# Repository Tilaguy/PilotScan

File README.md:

## PILOT SCAN
---
### 1. Descripción

En este repositorio se encuentran alojados los algoritmos necesarios para elaborar una interfaz de comunicación codificada con capacidad de detección de errores, durante el proceso de envío. Esta interfaz hace parte del sistema titulado **PilotScan\***, el cual consta de un sistema central de procesamiento y un sistema de respaldo que monitora de forma continua, el estado del sistema tanto a nivel hardware como software, además tiene la capacidad de realizar acciones indicadas por sistema central, sobre los diferentes módulos que conforman el sistema.

Para el sistema central de procesamiento, se usa una **Intel®️ NUC Board** con Linux 16.04 server. Para el sistema de respaldo se emplea un **dsPIC 30F4011**, el cual conecta diferentes sensores analógicos y digitales, tiene la capacidad de habilitar y deshabilitar fuentes reguladas de *12 V* y *24 V*, además de emitir mensajes al usuario a través de una bocina y leds RGB programables.

**\*** La información detallada del sistema se encuentra alojada en el repositorio: \ link \

---
## 2. Repository organization
Este repositorio se encuentra organizado de la siguiente forma:

### 2.1. PIC
* *Timer.c*:  Este archivo genera un reloj a frecuencia constante en un microcontrolador **PIC 16f506**, el cual sirve como base de tiempo para garantizar que el sistema de firmware está en funcionamiento.
### 2.2. Python
Estos archivos son nodos para ROS, los cuales interactúan entre sí por medio de tópicos para el monitoreo, procesamiento y acción sobre los diferentes módulos que conforman el sistema **PilotScan**.

* *Firmware.py*:  Nodo encargado de la recepción y transmisión serial con el sistema de respaldo.

* *Monitoring.py*:  Nodo encargado del procesamiento, codificación y decodificación de la información mediante protocolos diseñados para cada caso específico.

* *Resources.py*:  Nodo que lee la información del estado del sistema y la publica por medio de tópicos separados como el estado de memoria, la temperatura de los núcleos y entre otros.

### 2.3. dsPIC
#### 2.3.1. Include

* *ports.h*:  Librería para hacer asignaciones de pines según su uso y declaración de variables globales.

* *NOTAS.C*:  Librería para definir el tiempo de una nota usada por el Buzzer en el sistema.

* *TONOS.C*:  Librería donde se definen las notas musicales separado por octavas en 4 grupos de frecuencias diferentes.

* *SerialProtocol.h*:  Librería encargada de la codificación y decodificación de la información mediante protocolos diseñados para cada caso específico.

* *Hadware_actions.h*:  Librería usada para generar acciones o notificaciones del estado del sistema mediante el buzzer o los LEDs RGB.

* *Nuc_interface.h*:  Librería usada para encender y apagar el sistema de cómputo central.

* *I2C_DIR*:  Libreria que contiene las definiciones de direcciones I2C para la comunicación con algunos sensores, las funciones correspondientes para establecer dicha comunicación.

#### 2.3.2. Main
En el archivo main.c se hace uso de las librerías mencionadas anteriormente, se realiza la configuración de los diferentes periféricos de microcontrolador como modulo ADC, I2C, RS232, entre otros. Adicionalmente, se realiza la configuración y activación de interrupciones.

---

## 3. Protocolo de comunicación serial **computador-dsPIC**
El protocolo que se usa para la comunicación entre el microcontrolador y el computador genera un número que codifica la información en hexadecimal, esta codificación depende de quién es emisor del mensaje, esta codificación se explica más detalladamente a continuación. Además, el protocolo cuenta con un Byte de inicio (*'$'*) que indica el comienzo del mensaje y un salto de línea (*'\n'*) que informa el final. En cualquier caso, si los Bytes de información toman los valores de 0, significa un error en la codificación.

### 3.1. Protocolo de envió desde la Intel® NUC Board
Este protocolo se construye a partir de una tabla de valores constantes, los cuales indican el estado del sistema en diferentes ámbitos tales como: monitoreo y control de las fuentes, la comunicación de problemas de ejecución y otros requerimientos necesarios para el correcto funcionamiento del sistema. Dicho protocolo consta de dos Byte, los cuales codifican la información.

El primer Byte (**data1**) indica el origen de la información (VN-300, LiDAR, estado del sistema, etc.) de la cual se está dando a conocer su estado. El segundo Byte (**data2**) informa el estado y da idea de cómo debe proceder el microcontrolador. Los dos Bytes restantes corresponden al checksum, quien funciona como sistema de detección de errores en el proceso de comunicación, pues dichos Bytes deben corresponden a la suma de los dos primeros (**dato1+dato2**).

Cada mensaje es interpretado por el microcontrolador quien efectúa algún tipo de acción, ya sea realizando un encendido o apagado de algún elemento, activando alertas auditivas o alertas visuales a través de leds RGB.

* **P. ej.** Si la *temperatura media de los núcleos del sistema de cómputo* esta entre 35 °C y 40 °C, en microcontrolador debe *encender los ventiladores* en cierta forma particular.
  * Mensaje enviado:
  ~~~
  data1 =      0x4
  data2 =      0xE
  checksum =   0x12
  mensaje =    '$19986\n'
  ~~~
  * Acción tomada por el microcontrolador:
  ~~~
  - Encendido de ventilador ( PWM ~ 60% )
  - LED RGB 4 ([R,G,B] = [25,128,0])
  ~~~
#### Tabla 3.1.1. Mensajes del sistema.

data 1 | data 2 | message | meaning
-- | -- | -- | -- 
0 | 0 |         |Reserve
0 | 1 | sys-on_24 |	Turn-on source 24V
0 | 2 | sys-off_12 |Turn-off source 12V
0 | 3 | sys-off_24 |Turn-off source 24V
0 | 4 | sys-mem_E |	Memory problem
0 | 5 | sys-on_m8 |	Turn LiDAR on
0 | 6 | sys-on_tty |Turn all tty ports on
0 | 7 |
0 | 8 |
0 | 9 |
0 | A |
0 | B |
0 | C |
0 | D |
0 | E |
0 | F |

#### Tabla 3.1.2. Mensajes del estado del VN300.
data 1 | data 2 | message | meaning | R | G | B |LED
-- | -- | -- | -- | -- | -- | -- |--
1 | 0 |         |Reserve|0|0|0|L1
1 | 1 | VN300-NC |	VN300 No Connected|240|0|0|L1
1 | 2 | VN300-Start |VN 300 Starting|240|128|0|L1
1 | 3 | VN300-<25 | VN300 <25%|50|0|240|L1
1 | 4 | VN300-<50 |25% < VN300 <50%|50|80|160|L1
1 | 5 | VN300-<75 |	50% < VN300 <75|50|160|80|L1
1 | 6 | VN300->75 |VN300 >75%|50|240|0|L1
1 | 7 |VN300-Work | VN300 Working|0|240|0|L1
1 | 8 |
1 | 9 |
1 | A |
1 | B |
1 | C |
1 | D |
1 | E |
1 | F |

#### Tabla 3.1.3. Mensajes del estado del LiDAR M8.
data 1 | data 2 | message | meaning | R | G | B |LED
-- | -- | -- | -- | -- | -- | -- | --
2 | 0 |         |Reserve|0|0|0|L2
2 | 1 | M8-NC |	M8 No Ping|240	|0|0|L2
2 | 2 | M8-Start |M8 Starting|240|128|0|L2
2 | 3 |
2 | 4 |
2 | 5 |
2 | 6 |
2 | 7 |M8-Work | M8 Working|0|240|0 |L2
2 | 8 |
2 | 9 |
2 | A |
2 | B |
2 | C |
2 | D |
2 | E |
2 | F |
#### Tabla 3.1.4. Mensajes del estado de la cámara.
data 1 | data 2 | message | meaning
-- | -- | -- | --
3 | 0 |         |Reserve
3 | 1 | CAM-NC | CAM No Connected
3 | 2 | CAM-Start |CAM Starting
3 | 3 |  |
3 | 4 |  |
3 | 5 |  |
3 | 6 |  |
3 | 7 |CAM-Work | CAM Working
3 | 8 |
3 | 9 |
3 | A |
3 | B |
3 | C |
3 | D |
3 | E |
3 | F |
#### Tabla 3.1.5. Mensajes del control Fuzzy para temperatura.
data 1 | data 2 | message | meaning | R | G | B|LED
-- | -- | -- | -- | -- | -- | -- |--
3 | 0 |  |Reserve|0|0|0|L4
3 | 1 |   
3 | 2 |  
3 | 3 |  
3 | 4 |  
3 | 5 |  
3 | 6 |  
3 | 7 |   
3 | 8 |
3 | 9 |
3 | A |
3 | B |
3 | C |FUZZ-T1|>25°|13	|0|	125|L4
3 | D |FUZZ-T2|>30°|113|	0|	125|L4
3 | E |FUZZ-T3|>35°|255|	128|	0|L4
3 | F |FUZZ-T4|>40°|250|0|	0|L4
#### Tabla 3.1.6. Mensajes de error de memoria.
data 1 | data 2 | message | meaning | R | G | B |LED
-- | -- | -- | -- | -- | -- | -- | --
A | 0 |  |Reserve|0|0|0|L3
A | 1 | memo-RAM_E1 |RAM alert1|255|64|64|L3
A | 2 | memo-RAM_E2 |RAM alert2|255|0|0|L3
A | 3 |
A | 4 |
A | 5 |
A | 6 | memo-ROM_E1 |ROM alert1|64|133|255 |L3
A | 7 | memo-ROM_E2 |ROM alert2|64|64|255|L3
A | 8 | memo-ROM_E3 |ROM alert3|0|0|255|L3
A | 9 |
A | A |
A | B |
A | C |
A | D |
A | E |
A | F |
### 3.2. Protocolo de envío desde el dsPIC
Este protocolo se construye a partir de una tabla de valores constantes y los datos numéricos codificados en hexadecimal, que informan al computador sobre las variables medidas por el microcontrolador. Dicho protocolo consta de tres Bytes que codifican la información, los cuales son enviados al computador para ponerlo en conocimiento de los valores numéricos de las variables fundamentales para el funcionamiento de las tarjetas.

El primer Byte corresponde al tipo de información (**command**) como corrientes, voltajes, etc., y su origen. Los siguientes dos Bytes son la información numérica codificada (**data1**, **data2**), la cual puede ser entera o flotante. Adicionalmente, existen dos Bytes corresponden al checksum, el cual permite verificar la información transmitida como protocolo de detección de errores y además permite conocer si el dato numérico enviado es un entero con rango [0, 255] (**command+data1+data2+0x05**), o un flotante con una cifra decimal de precisión (**command+data1+data2**).

* **P. ej.** La *corriente proveniente de la fuente de 5 V* medida por el sensor es de *0.45 A*, a su vez *el altímetro* detecta una altura de *64 m*.
  * Mensaje 1 enviado:
  ~~~
  Command =    0x1
  data1 =      0x0
  data2 =      0x4
  checksum =   0x05
  mensaje =    '$66565\n'
  ~~~
  * Mensaje 2 enviado:
  ~~~
  Command =    0xD
  data1 =      0x4
  data2 =      0x0
  checksum =   0x16
  mensaje =    '$868374\n'
  ~~~
#### Tabla 3.2.1. Variables medidas codificadas.
   
Command|	data1|	data2|	meaning|
|--|--|--|--|
0|	|	|	Reserved|
1|	x|	y|	current source 5 "x.y"|
2|	x|	y|	current source 12 "x.y"|
3|	x|	y|	current source 24 "x.y"|
4|	x|	y|	current source battery "x.y"|
5|	x|	y|	Voltage source 5 "x.y"|
6|	x|	y|	Voltage source 12 "x.y"|
7|	x|	y|	Voltage source 24 "x.y"|
8|	x|	y|	Voltage source Battery "x.y"|
9|	x|	y|	Temperature LiDAR|
A|	x|	y|	Temperature dsPIC|
B|	x|	y|	Temperature DC|
C|	x|	y|	Temperature xx|
D|	x|	y|	Hight|

#### Tabla 3.2.2. Estado de los módulos del sistema.
|Command|	data1|	data2|	meaning|
|--|--|--|--|
|F	|0	|0	|Reserved|
|F	|0	|1	|12 V is on|
|F	|1	|0	|24 V is on|
|F	|1	|1	|All sources are on|
|F	|0	|2	|12 V is going to shut it down in 1 m|
|F	|2	|0	|24 V is going to shut it down in 1 m|
|F	|2	|2	|All sources are going to shut it down in 1 m|
|F	|0	|3	|shut LiDAR down |
|F	|3	|0	|close all tty ports|
|F	|3	|3	|shut ROS down |
|F	|0	|4	|turn LiDAR on|
|F	|4	|0	|turn all tty ports on|
|F	|4	|4	|turn ROS on|

---

### 4. Software requirements for computer

#### 4.1. ROS Kinetic instaliation

To install robot operating system (ROS) in the kinetic version for ubuntu 16.04, you should follow the steeps descrived in http://wiki.ros.org/kinetic/Installation/Ubuntu.

#### 4.2. VN300 ROS node

The installing of VN-300 node for ROS, it begins with downloading the repository in *workspace/src* directory.
~~~
$ git clone https://github.com/HaroldMurcia/vectornav.git
~~~
Afeter that, you have to compilate the *workspace* directory.
~~~
$ catkin_make
$ source devel/setup.bash
~~~
Finaly, The node could be launched with ROS instrction:
~~~
$ roslaunch vectornav vectornav.launch
~~~
#### 4.3. Quanergy M8 liDAR

To be able to launch the ROS node of Quanergy M8 LiDAR, you have to follow the steeps of the next repository.
https://github.com/mfassler/python3-quanergyM8

#### 4.1. System_monitor Installation
La instalación del System_monitor node para ROS: (https://github.com/RobotnikAutomation/system_monitor)

Dentro de la carpeta *src* del *workspace*, se debe descargar el *system_monitor* usando la siguiente instrucción:
~~~
$ git clone https://github.com/RobotnikAutomation/system_monitor
~~~
Es necesario instalar algunas dependencias adicionales para su ejecución,
~~~
$ sudo apt-get install sysstat ifstat ntpdate
~~~
Luego, se compila en el *workspace* y se asigna el directorio *devel*,
~~~
$ catkin_make
$ source devel/setup.bash
~~~
Por último, para lanzar el nodo se usa la instrucción:
~~~
$ roslaunch system_monitor system_monitor.launch
~~~

---
### 5. Authors.

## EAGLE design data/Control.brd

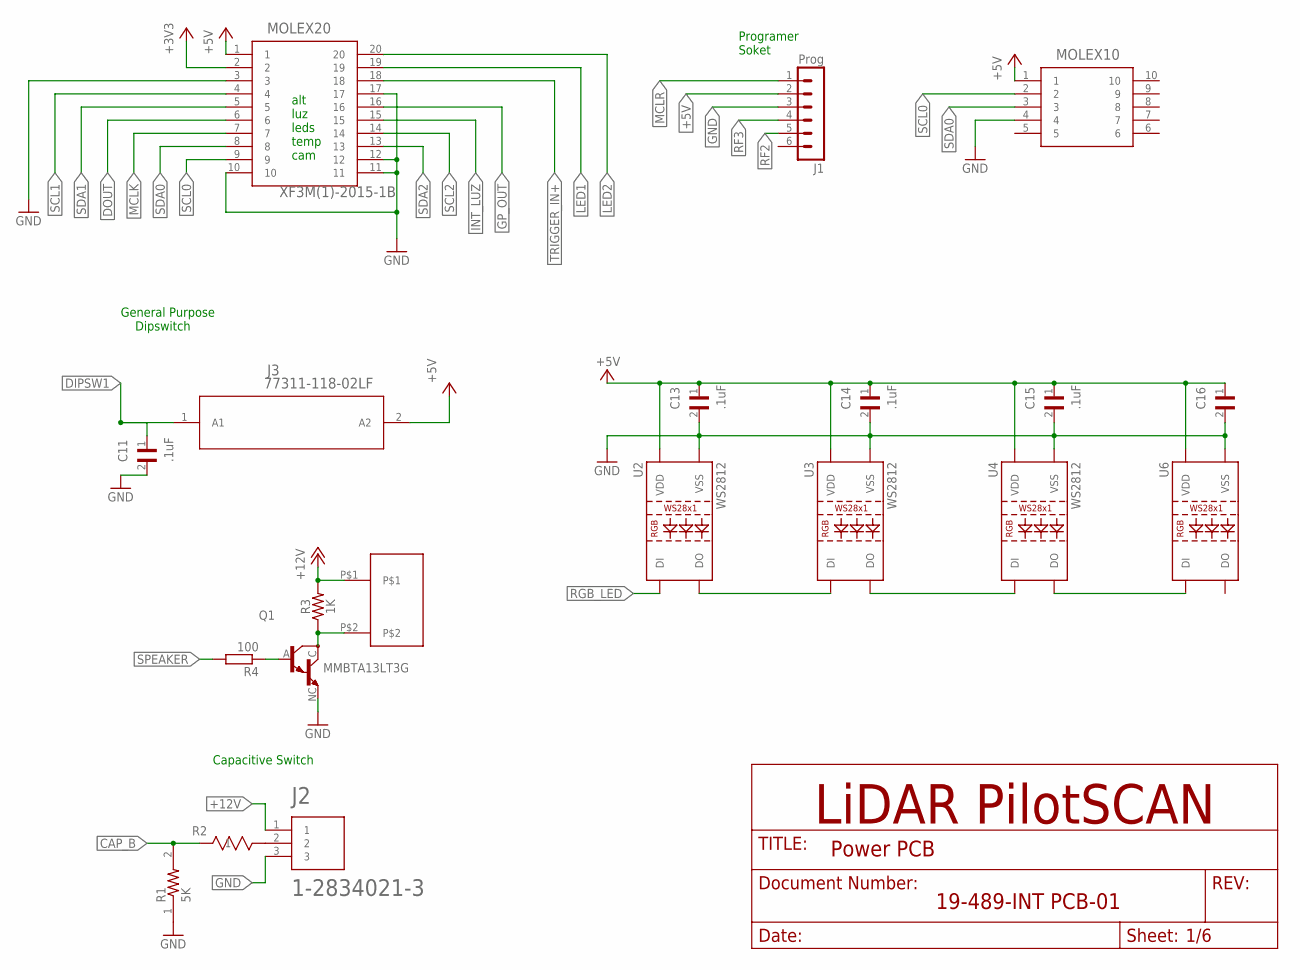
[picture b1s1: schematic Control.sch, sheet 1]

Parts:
BUZZ1: PS1240P02BT
C11, C13, C14, C15, C16: .1uF; CAPC2012X140N
J1: Prog; MA06-1
J2: 1-2834021-3; CONN_1-2834021-3
J3: 77311-118-02LF
MOLEX10: 522071060
MOLEX20: XF3M(1)-2015-1B
Q1: MMBTA13LT3G
R1: 5K; RESC2012X60
R2: 6K8; RES_RC0201_P6XP3
R3: 1K; AXIAL-0.3
R4: 100; RMCF0805JT270R
U2, U3, U4, U6: WS2812; LED-TRICOLOR-5050-IC

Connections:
+3V3: MOLEX20.2; also elsewhere on the board
+5V: C13.1, C14.1, C15.1, C16.1, J1.2, J3.2 (A2), MOLEX10.1, MOLEX20.1, U2.3 (VDD), U2.5 (VDD), U3.3 (VDD), U3.5 (VDD), U4.3 (VDD), U4.5 (VDD), U6.3 (VDD), U6.5 (VDD); also elsewhere on the board
+12V: BUZZ1.P$1, J2.1, R3.P$2 (2); also elsewhere on the board
CAP_B: R1.2, R2.1; also elsewhere on the board
DIPSW1: C11.1, J3.1 (A1); also elsewhere on the board
DOUT: MOLEX20.6; also elsewhere on the board
GND: C11.2, C13.2, C14.2, C15.2, C16.2, J1.3, J2.3, MOLEX10.4, MOLEX20.3, MOLEX20.10, MOLEX20.11, MOLEX20.12, MOLEX20.17, Q1.NC (E), R1.1, U2.6 (VSS), U3.6 (VSS), U4.6 (VSS), U6.6 (VSS); also elsewhere on the board
GP_OUT: MOLEX20.16; also elsewhere on the board
INT_LUZ: MOLEX20.15; also elsewhere on the board
LED1: MOLEX20.19; also elsewhere on the board
LED2: MOLEX20.20; also elsewhere on the board
MCLK: MOLEX20.7; also elsewhere on the board
MCLR: J1.1; also elsewhere on the board
unnamed: Q1.A (B), R4.1
unnamed: BUZZ1.P$2, Q1.C, R3.P$1 (1)
unnamed: J2.2, R2.2
unnamed: U2.1 (DO), U3.2 (DI)
unnamed: U3.1 (DO), U4.2 (DI)
unnamed: U4.1 (DO), U6.2 (DI)
RF2: J1.5; also elsewhere on the board
RF3: J1.4; also elsewhere on the board
RGB_LED: U2.2 (DI); also elsewhere on the board
SCL0: MOLEX10.2, MOLEX20.9; also elsewhere on the board
SCL1: MOLEX20.4; also elsewhere on the board
SCL2: MOLEX20.14; also elsewhere on the board
SDA0: MOLEX10.3, MOLEX20.8; also elsewhere on the board
SDA1: MOLEX20.5; also elsewhere on the board
SDA2: MOLEX20.13; also elsewhere on the board
SPEAKER: R4.2; also elsewhere on the board
TRIGGER_IN+: MOLEX20.18; also elsewhere on the board

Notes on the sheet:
Programer Soket
General Purpose Dipswitch
Capacitive Switch
alt luz leds temp cam

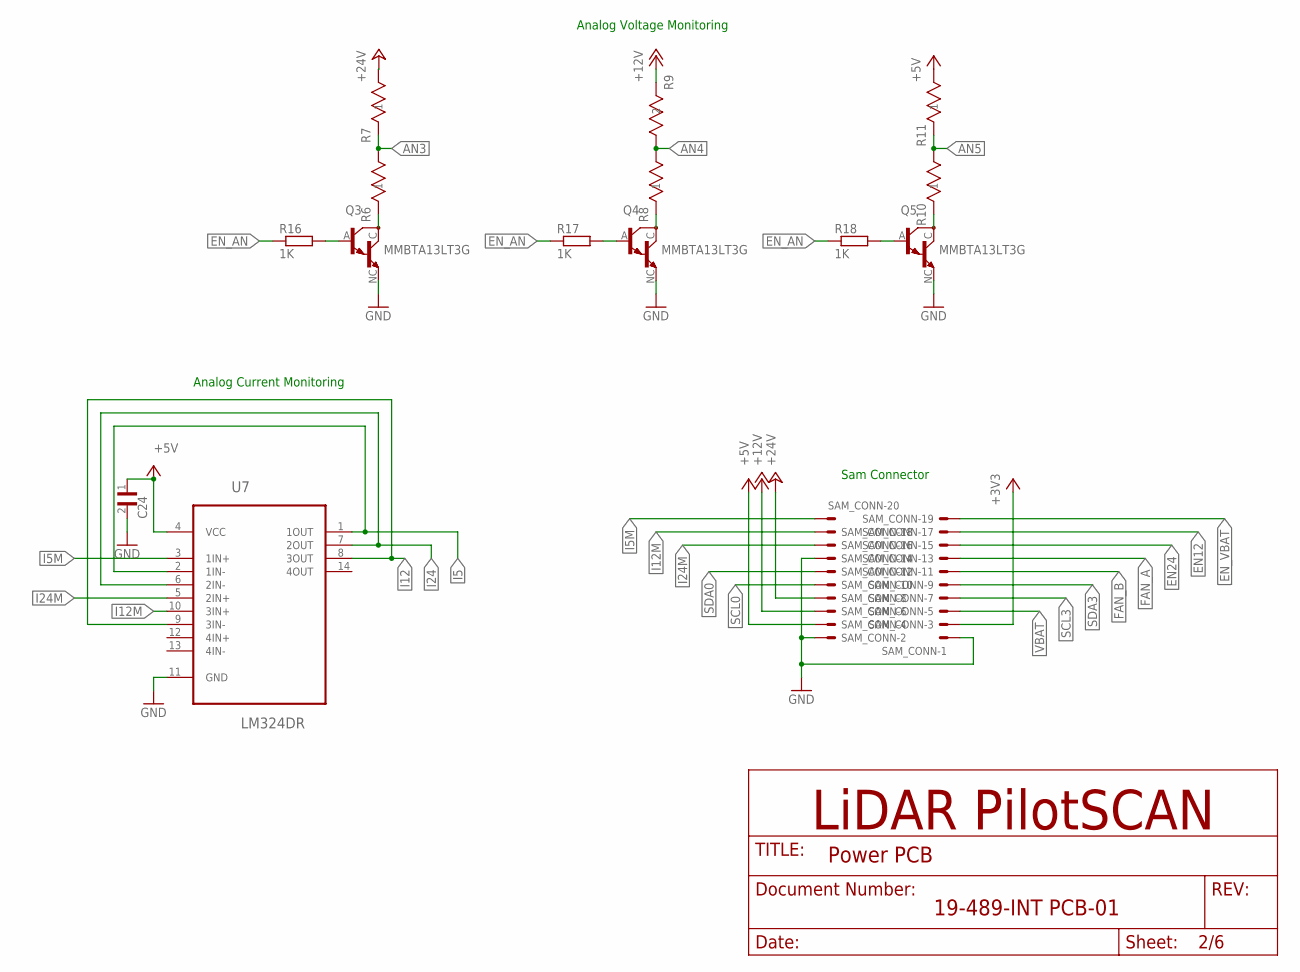
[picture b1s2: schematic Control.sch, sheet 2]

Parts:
C24: 08056C104JAZ2A; CAPC2012X140N
Q3, Q4, Q5: MMBTA13LT3G
R6, R8, R10: 1K8; RES_RC0201_P6XP3
R7: 18K; RES_RC0201_P6XP3
R9: 8K2; RES0805_CRG_TYCO-L
R11: 1K5; YAG_R0201
R16, R17, R18: 1K; RMCF0805FT1K00
SAM_CONN: IPT1-110-01-L-D
U7: LM324DR; SOIC127P600X175-14N

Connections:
+3V3: SAM_CONN.P$3; also elsewhere on the board
+5V: C24.1, R11.2, SAM_CONN.P$4, U7.4 (VCC); also elsewhere on the board
+12V: R9.2, SAM_CONN.P$6; also elsewhere on the board
+24V: R7.2, SAM_CONN.P$8
AN3: R6.2, R7.1; also elsewhere on the board
AN4: R8.2, R9.1; also elsewhere on the board
AN5: R10.2, R11.1; also elsewhere on the board
EN12: SAM_CONN.P$17; also elsewhere on the board
EN_AN: R16.1, R17.1, R18.1; also elsewhere on the board
EN_VBAT: SAM_CONN.P$19; also elsewhere on the board
ESRDTFYGHUJI: Q4.C, R8.1
FAN_A: SAM_CONN.P$13; also elsewhere on the board
FAN_B: SAM_CONN.P$11; also elsewhere on the board
GND: C24.2, Q3.NC (E), Q4.NC (E), Q5.NC (E), SAM_CONN.P$1, SAM_CONN.P$2, SAM_CONN.P$14, U7.11 (GND); also elsewhere on the board
I5: U7.1 (1OUT), U7.2 (1IN-); also elsewhere on the board
I5M: SAM_CONN.P$20, U7.3 (1IN+)
I12: U7.8 (3OUT), U7.9 (3IN-); also elsewhere on the board
I12M: SAM_CONN.P$18, U7.10 (3IN+)
I24: U7.6 (2IN-), U7.7 (2OUT); also elsewhere on the board
I24M: SAM_CONN.P$16, U7.5 (2IN+)
unnamed: Q3.A (B), R16.2
unnamed: Q3.C, R6.1
unnamed: Q4.A (B), R17.2
unnamed: Q5.C, R10.1
unnamed: Q5.A (B), R18.2
SCL0: SAM_CONN.P$10; also elsewhere on the board
SCL3: SAM_CONN.P$7; also elsewhere on the board
SDA0: SAM_CONN.P$12; also elsewhere on the board
SDA3: SAM_CONN.P$9; also elsewhere on the board
VBAT: SAM_CONN.P$5; also elsewhere on the board

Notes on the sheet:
Analog Voltage Monitoring
Analog Current Monitoring
Sam Connector

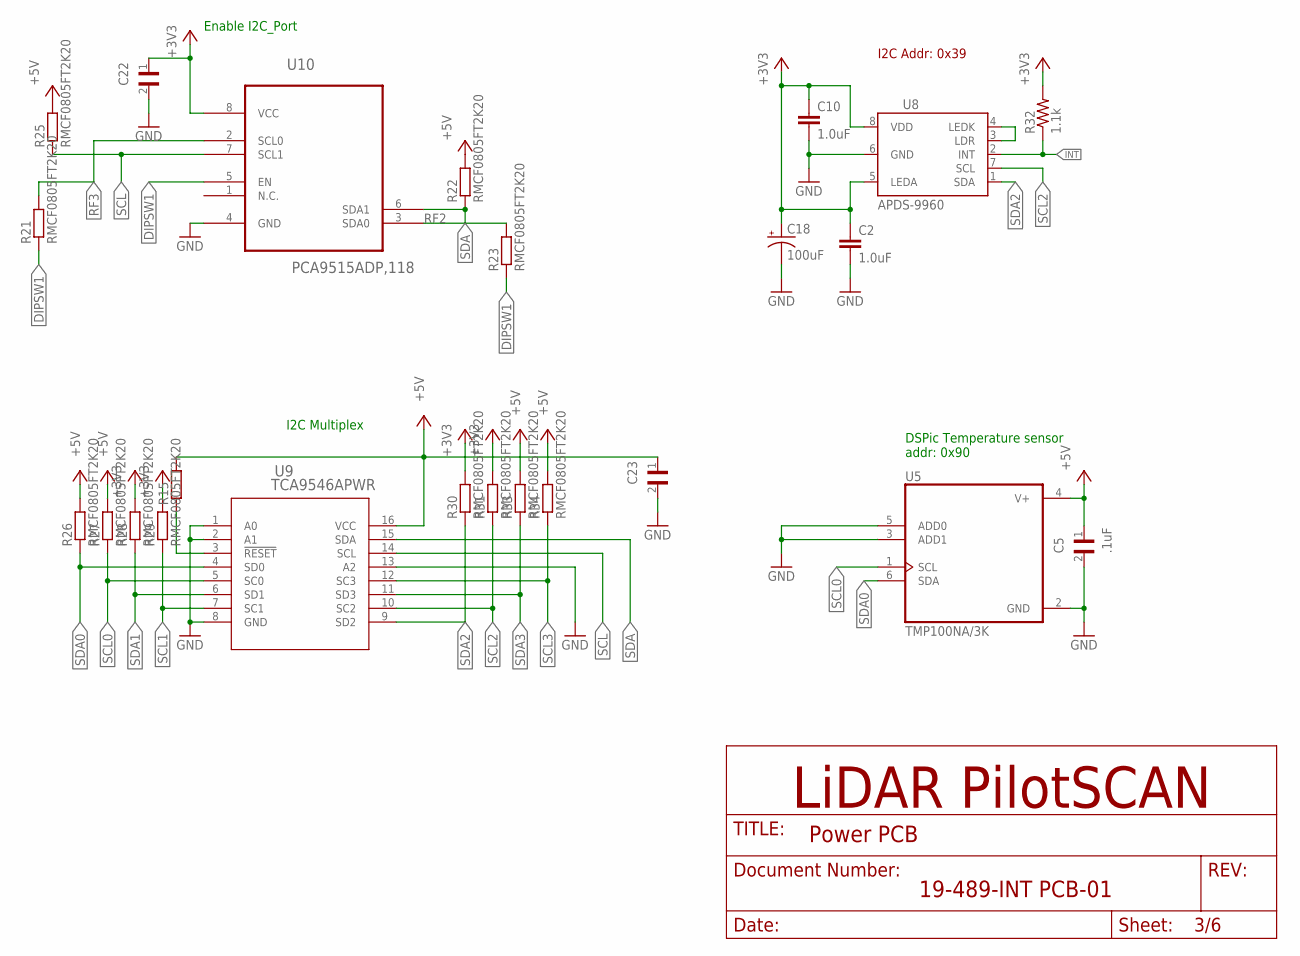
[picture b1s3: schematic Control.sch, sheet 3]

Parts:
C2, C10: 1.0uF; 0603-CAP
C5: .1uF; CAPC2012X140N
C18: 100uF; EIA7343
C22, C23: 08056C104JAZ2A; CAPC2012X140N
R15, R21, R22, R23, R25, R26, R27, R28, R29, R30, R31, R33, R34: RMCF0805FT2K20
R32: 1.1k; 0603-RES
U5: TMP100NA/3K
U8: APDS-9960
U9: TCA9546APWR; PW16
U10: PCA9515ADP,118; SOP65P490X110-8N

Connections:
+3V3: C2.1, C10.1, C18.A (+), C22.1, R28.2, R29.2, R30.2, R31.2, R32.2, U8.5 (LEDA), U8.8 (VDD), U10.8 (VCC); also elsewhere on the board
+5V: C5.1, C23.1, R15.2, R22.2, R25.2, R26.2, R27.2, R33.2, R34.2, U5.4 (V+), U9.16 (VCC); also elsewhere on the board
DIPSW1: R21.1, R23.1, U10.5 (EN); also elsewhere on the board
GND: C2.2, C5.2, C10.2, C18.C (-), C22.2, C23.2, U5.2 (GND), U5.3 (ADD1), U5.5 (ADD0), U8.6 (GND), U9.1 (A0), U9.2 (A1), U9.8 (GND), U9.13 (A2), U10.4 (GND); also elsewhere on the board
INT: R32.1, U8.2 (INT)
unnamed: U8.3 (LDR), U8.4 (LEDK)
unnamed: R15.1, U9.3 (!RESET)
RF2: R23.2, U10.3 (SDA0); also elsewhere on the board
RF3: R21.2, U10.2 (SCL0); also elsewhere on the board
SCL: R25.1, U9.14 (SCL), U10.7 (SCL1)
SCL0: R27.1, U5.1 (SCL), U9.5 (SC0); also elsewhere on the board
SCL1: R29.1, U9.7 (SC1); also elsewhere on the board
SCL2: R31.1, U8.7 (SCL), U9.10 (SC2); also elsewhere on the board
SCL3: R34.1, U9.12 (SC3); also elsewhere on the board
SDA: R22.1, U9.15 (SDA), U10.6 (SDA1)
SDA0: R26.1, U5.6 (SDA), U9.4 (SD0); also elsewhere on the board
SDA1: R28.1, U9.6 (SD1); also elsewhere on the board
SDA2: R30.1, U8.1 (SDA), U9.9 (SD2); also elsewhere on the board
SDA3: R33.1, U9.11 (SD3); also elsewhere on the board

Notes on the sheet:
Enable I2C_Port
I2C Addr: 0x39
I2C Multiplex
DSPic Temperature sensor addr: 0x90

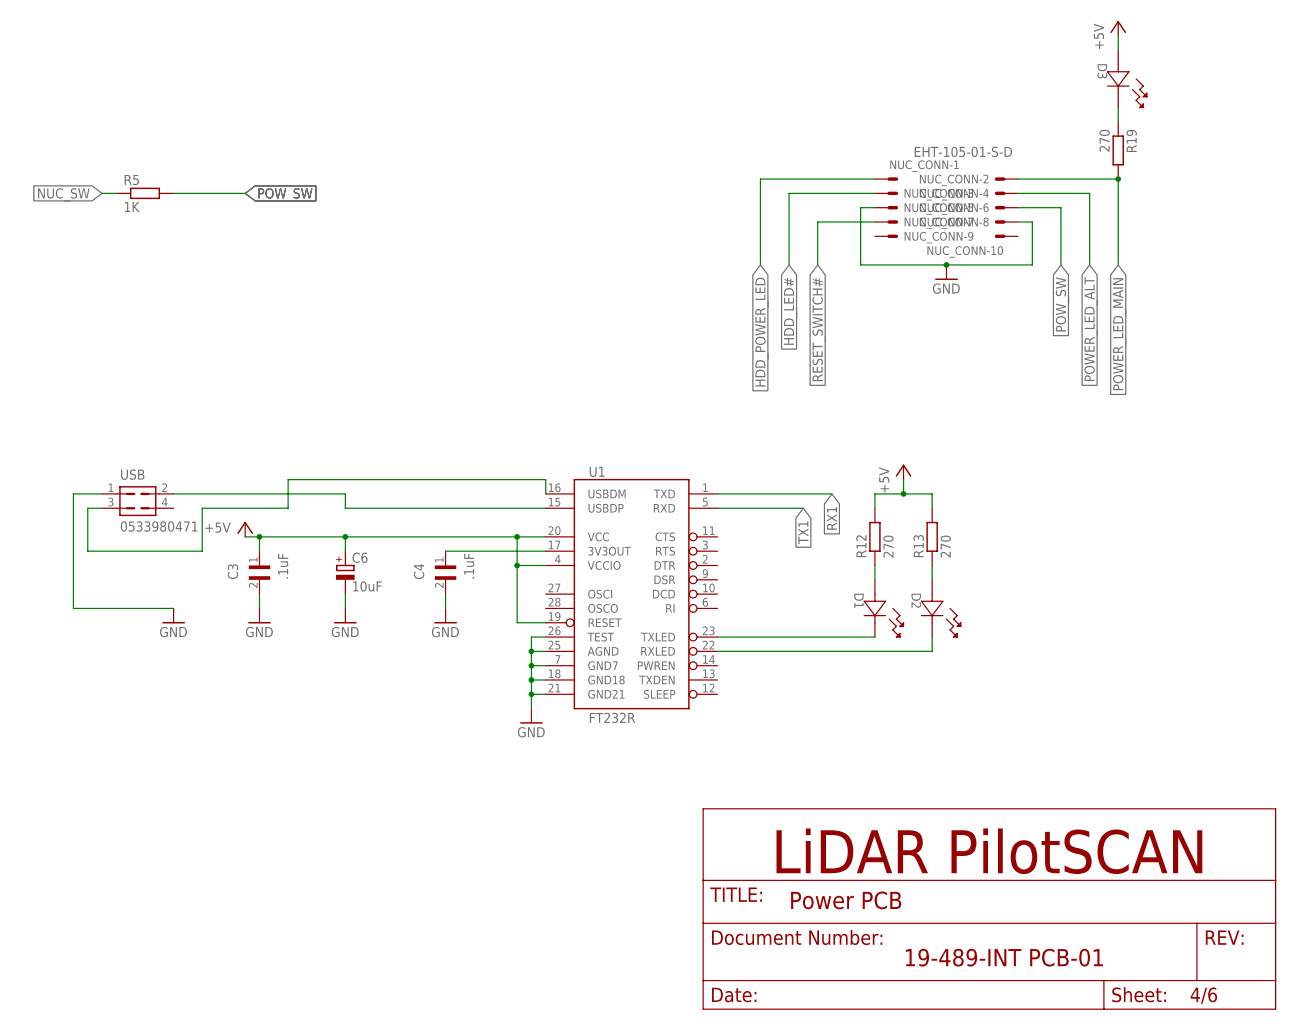
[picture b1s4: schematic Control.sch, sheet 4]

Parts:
C3, C4: .1uF; CAPC2012X140N
C6: 10uF; E1,8-4
D1, D2, D3: TLMS1100-GS08; LED_VISHAY_TLMX1100
NUC_CONN: EHT-105-01-S-D; 332-10
R5: 1K; RMCF0805FT1K00
R12, R13, R19: 270; RMCF0805JT270R
U1: FT232R; SSOP28DB
USB: 0533980471

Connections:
+5V: C3.1, C6.+, D3.2, R12.2, R13.2, U1.4 (VCCIO), U1.19 (RESET), U1.20 (VCC); also elsewhere on the board
GND: C3.2, C4.2, C6.-, NUC_CONN.5, NUC_CONN.8, U1.7 (GND7), U1.18 (GND18), U1.21 (GND21), U1.25 (AGND), U1.26 (TEST), USB.1; also elsewhere on the board
HDD_LED#: NUC_CONN.3
HDD_POWER_LED: NUC_CONN.1
unnamed: D1.2, R12.1
unnamed: C4.1, U1.17 (3V3OUT)
unnamed: D2.2, R13.1
unnamed: D3.1, R19.1
unnamed: U1.15 (USBDP), USB.2
unnamed: U1.16 (USBDM), USB.3
NUC_SW: R5.1; also elsewhere on the board
POWER_LED_ALT: NUC_CONN.4
POWER_LED_MAIN: NUC_CONN.2, R19.2; also elsewhere on the board
POW_SW: NUC_CONN.6, R5.2
RESET_SWITCH#: NUC_CONN.7
RX1: U1.1 (TXD); also elsewhere on the board
RXLED: D2.1, U1.22 (RXLED)
TX1: U1.5 (RXD); also elsewhere on the board
TXLED: D1.1, U1.23 (TXLED)

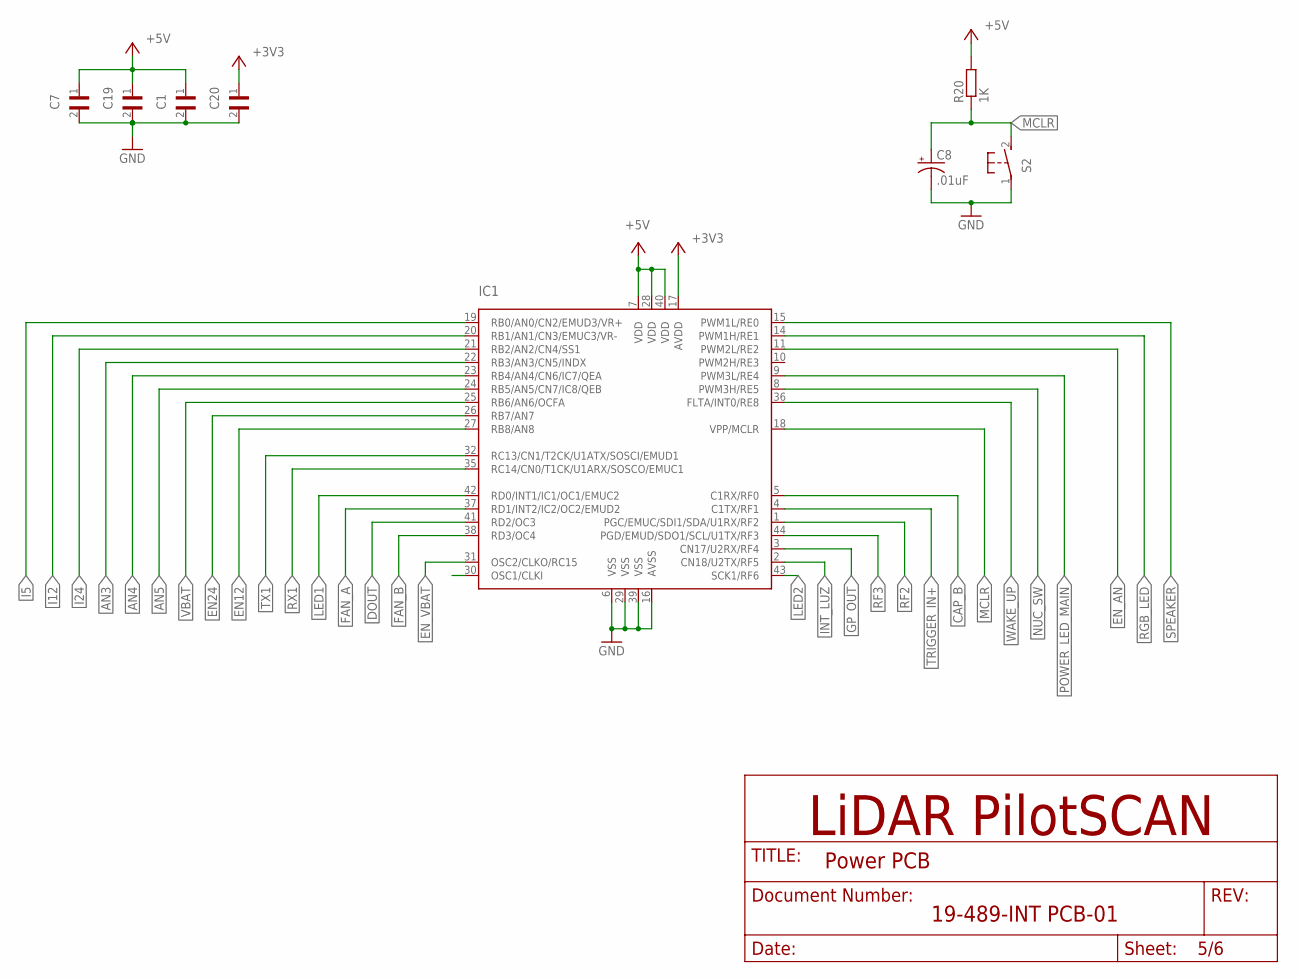
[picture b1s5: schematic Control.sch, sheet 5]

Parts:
C1, C7, C19, C20: 08056C104JAZ2A; CAPC2012X140N
C8: .01uF; CL03A104KQ3NNNC
IC1: DSPIC30F4011/PT; TQFP44
R20: 1K; RMCF0805FT1K00
S2: DTSM-3

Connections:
+3V3: C20.1, IC1.17 (AVDD); also elsewhere on the board
+5V: C1.1, C7.1, C19.1, IC1.7 (VDD), IC1.28 (VDD), IC1.40 (VDD), R20.2; also elsewhere on the board
AN3: IC1.22 (RB3/AN3/CN5/INDX); also elsewhere on the board
AN4: IC1.23 (RB4/AN4/CN6/IC7/QEA); also elsewhere on the board
AN5: IC1.24 (RB5/AN5/CN7/IC8/QEB); also elsewhere on the board
CAP_B: IC1.5 (C1RX/RF0); also elsewhere on the board
DOUT: IC1.41 (RD2/OC3); also elsewhere on the board
EN12: IC1.27 (RB8/AN8); also elsewhere on the board
EN_AN: IC1.11 (PWM2L/RE2); also elsewhere on the board
EN_VBAT: IC1.31 (OSC2/CLKO/RC15); also elsewhere on the board
FAN_A: IC1.37 (RD1/INT2/IC2/OC2/EMUD2); also elsewhere on the board
FAN_B: IC1.38 (RD3/OC4); also elsewhere on the board
GND: C1.2, C7.2, C8.2 (-), C19.2, C20.2, IC1.6 (VSS), IC1.16 (AVSS), IC1.29 (VSS), IC1.39 (VSS), S2.1; also elsewhere on the board
GP_OUT: IC1.3 (CN17/U2RX/RF4); also elsewhere on the board
I5: IC1.19 (RB0/AN0/CN2/EMUD3/VR+); also elsewhere on the board
I12: IC1.20 (RB1/AN1/CN3/EMUC3/VR-); also elsewhere on the board
I24: IC1.21 (RB2/AN2/CN4/SS1); also elsewhere on the board
INT_LUZ: IC1.2 (CN18/U2TX/RF5); also elsewhere on the board
LED1: IC1.42 (RD0/INT1/IC1/OC1/EMUC2); also elsewhere on the board
LED2: IC1.43 (SCK1/RF6); also elsewhere on the board
MCLR: C8.1 (+), IC1.18 (VPP/MCLR), R20.1, S2.2; also elsewhere on the board
NUC_SW: IC1.8 (PWM3H/RE5); also elsewhere on the board
POWER_LED_MAIN: IC1.9 (PWM3L/RE4); also elsewhere on the board
RF2: IC1.1 (PGC/EMUC/SDI1/SDA/U1RX/RF2); also elsewhere on the board
RF3: IC1.44 (PGD/EMUD/SDO1/SCL/U1TX/RF3); also elsewhere on the board
RGB_LED: IC1.14 (PWM1H/RE1); also elsewhere on the board
RX1: IC1.35 (RC14/CN0/T1CK/U1ARX/SOSCO/EMUC1); also elsewhere on the board
SPEAKER: IC1.15 (PWM1L/RE0); also elsewhere on the board
TRIGGER_IN+: IC1.4 (C1TX/RF1); also elsewhere on the board
TX1: IC1.32 (RC13/CN1/T2CK/U1ATX/SOSCI/EMUD1); also elsewhere on the board
VBAT: IC1.25 (RB6/AN6/OCFA); also elsewhere on the board
WAKE_UP: IC1.36 (FLTA/INT0/RE8); also elsewhere on the board

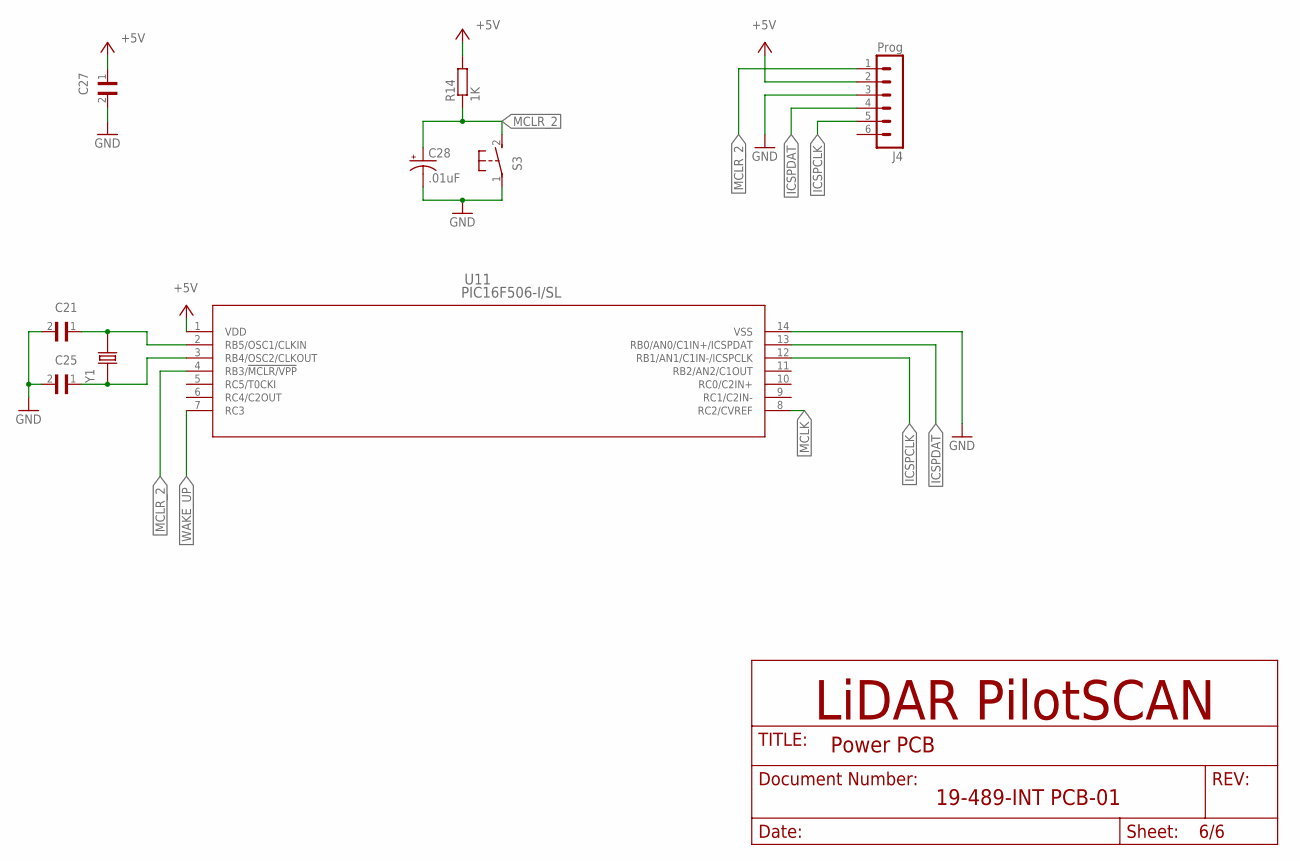
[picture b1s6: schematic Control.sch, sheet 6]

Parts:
C21, C25: C0603C150M8GACTU; CAPC1608X90
C27: 08056C104JAZ2A; CAPC2012X140N
C28: .01uF; CL03A104KQ3NNNC
J4: Prog; MA06-1
R14: 1K; RMCF0805FT1K00
S3: DTSM-3
U11: PIC16F506-I/SL; SOIC14-N_MC
Y1: ECS-10-13-1XH; XTAL_ECS-10-13-1XH

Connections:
+5V: C27.1, J4.2, R14.2, U11.1 (VDD); also elsewhere on the board
GND: C21.2, C25.2, C27.2, C28.2 (-), J4.3, S3.1, U11.14 (VSS); also elsewhere on the board
ICSPCLK: J4.5, U11.12 (RB1/AN1/C1IN-/ICSPCLK)
ICSPDAT: J4.4, U11.13 (RB0/AN0/C1IN+/ICSPDAT)
LVP: J4.6
MCLK: U11.8 (RC2/CVREF); also elsewhere on the board
MCLR_2: C28.1 (+), J4.1, R14.1, S3.2, U11.4 (RB3/!MCLR/VPP)
unnamed: C21.1, U11.2 (RB5/OSC1/CLKIN), Y1.2
unnamed: C25.1, U11.3 (RB4/OSC2/CLKOUT), Y1.1
WAKE_UP: U11.7 (RC3); also elsewhere on the board

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
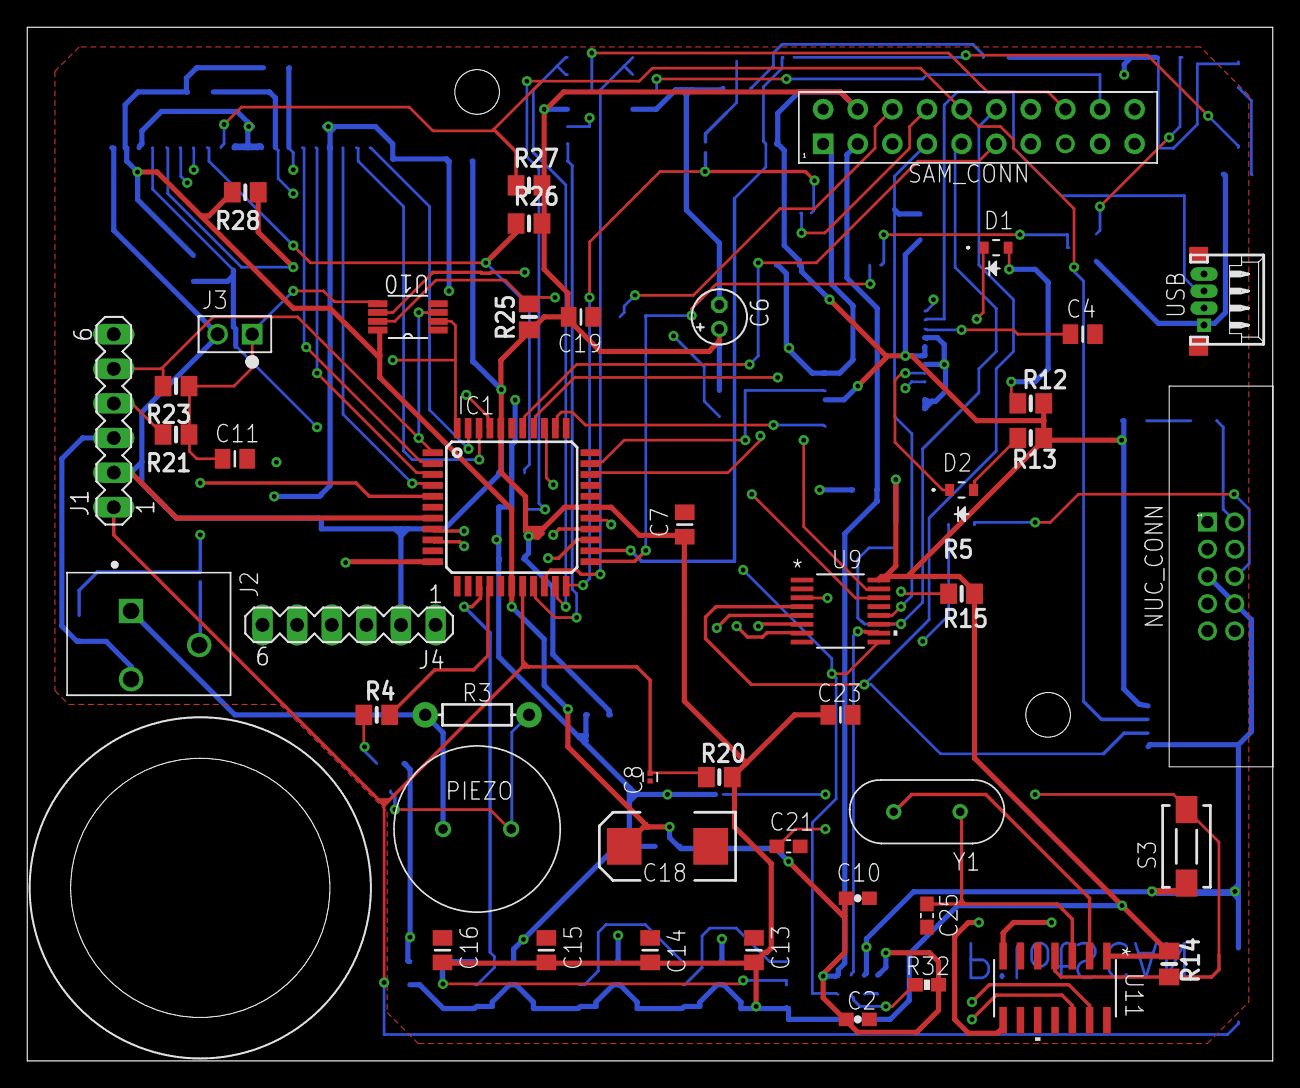
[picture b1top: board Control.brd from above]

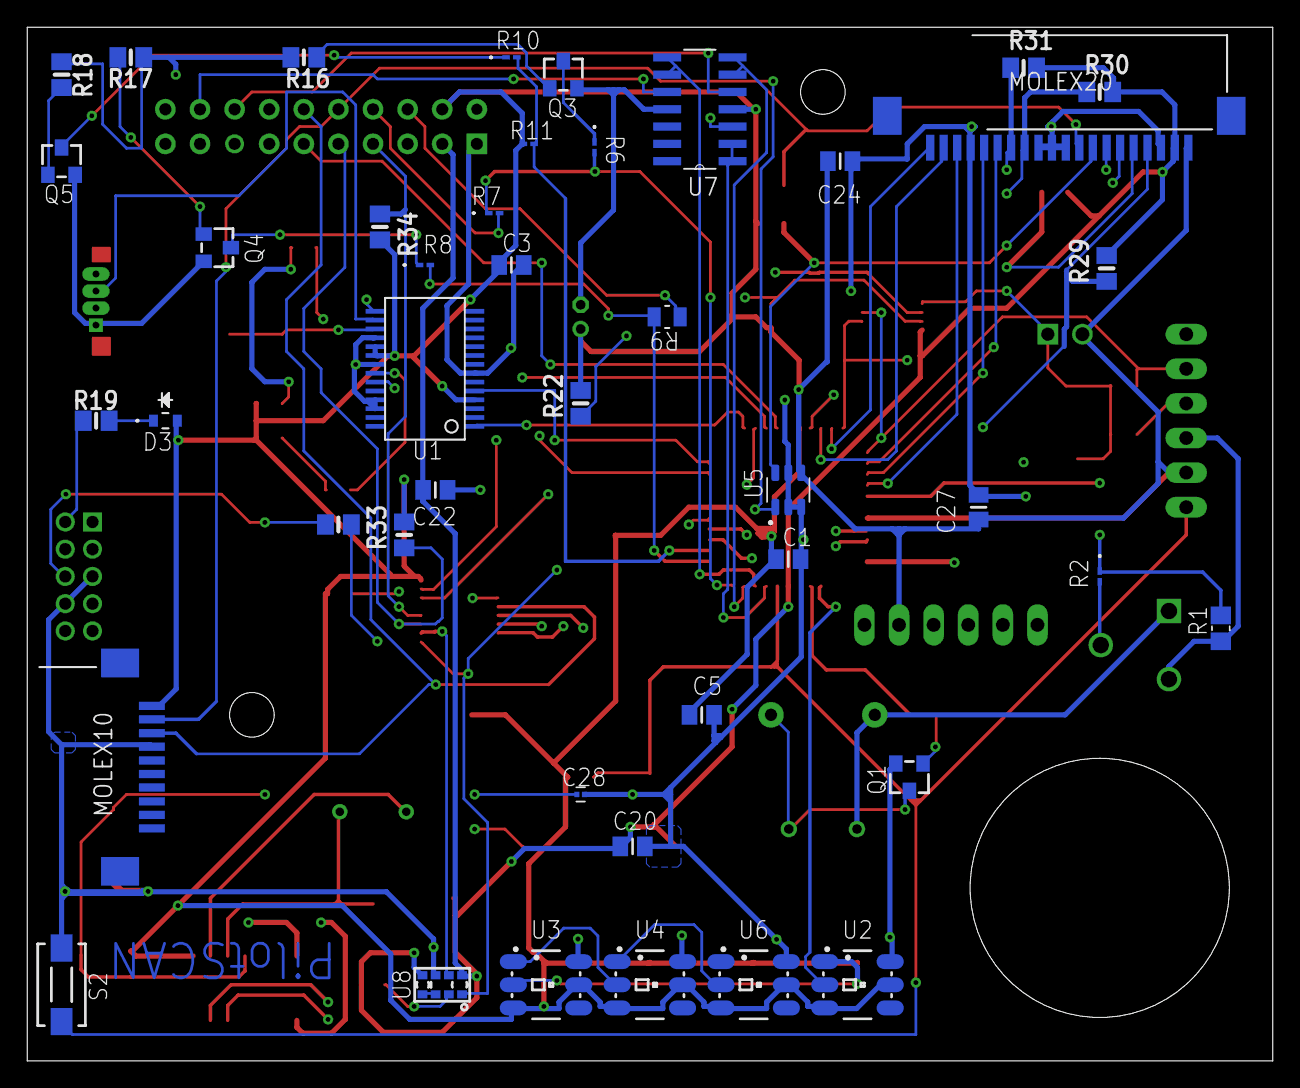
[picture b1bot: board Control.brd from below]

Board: 4 copper layers, 91.4 x 75.9 mm, 89 parts (43 on the bottom side), 79 nets.

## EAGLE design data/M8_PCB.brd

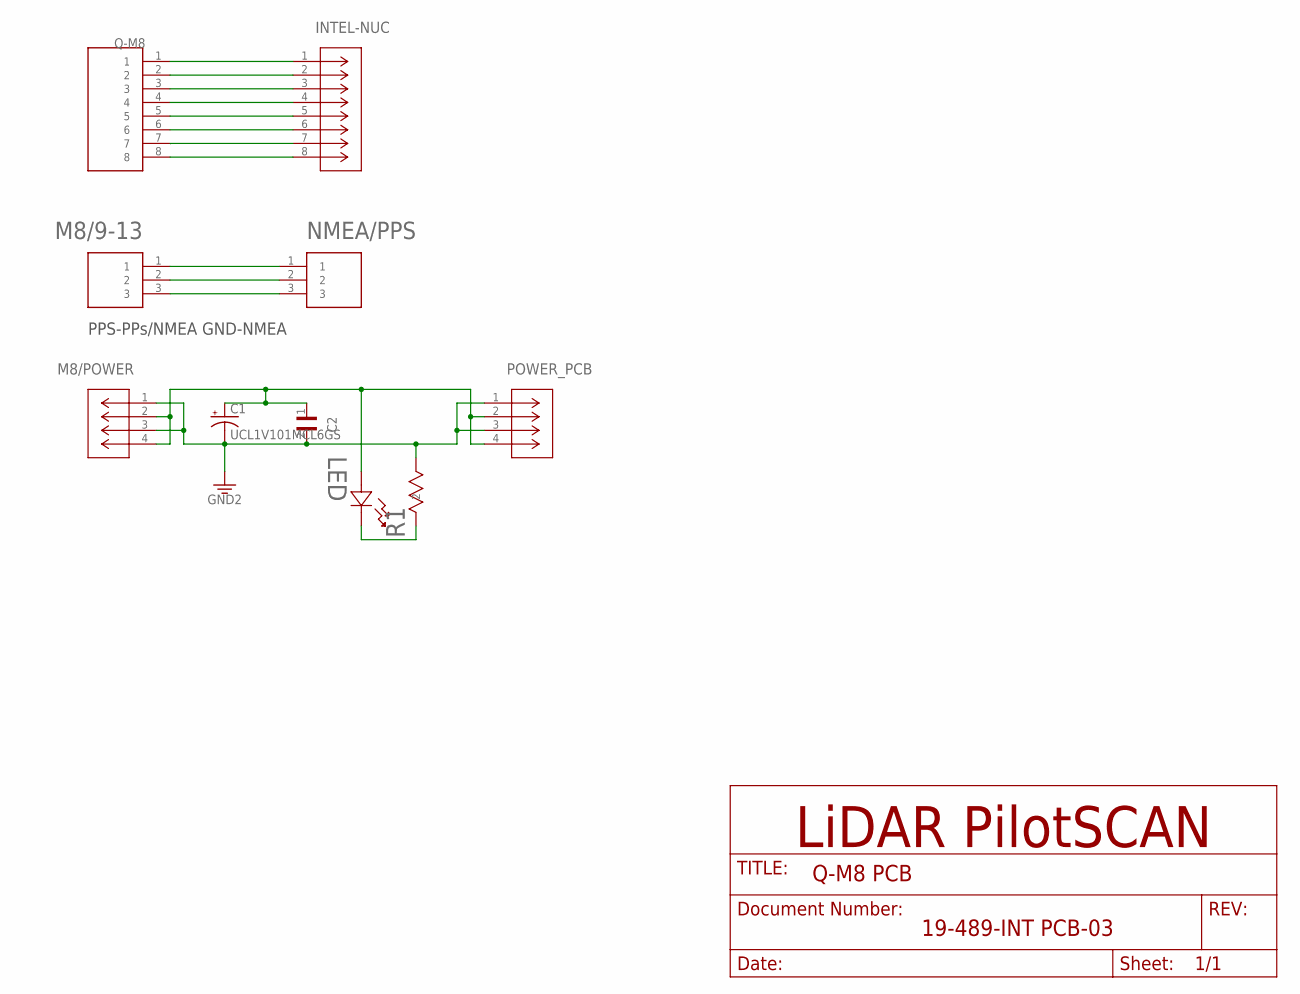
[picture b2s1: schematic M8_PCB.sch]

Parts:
C1: UCL1V101MCL6GS; U2-K
C2: GRM033R6YA104KE14D; CAPC0603X33N
INTEL-NUC: LLC; 0955032881
LED: VLMC3100-GS08; LED_PLCC_VSMB
M8/9-13: 1-2834021-3; CONN_1-2834021-3
M8/POWER: 3-794630-4; CON4_2X2_P3MM_VMNL2
NMEA/PPS: 1-2834021-3; CONN_1-2834021-3
POWER_PCB: 3-794630-4; CON4_2X2_P3MM_VMNL2
Q-M8: 292133-8; TE_292133-8
R1: CRCW04026K80FKEDHP; RES_CRCW_0402

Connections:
GROUND: C1.2 (-), C2.2, M8/POWER.1, M8/POWER.3, POWER_PCB.1, POWER_PCB.3, R1.1
unnamed: INTEL-NUC.1, Q-M8.1
unnamed: INTEL-NUC.2, Q-M8.2
unnamed: INTEL-NUC.3, Q-M8.3
unnamed: INTEL-NUC.4, Q-M8.4
unnamed: INTEL-NUC.5, Q-M8.5
unnamed: INTEL-NUC.6, Q-M8.6
unnamed: INTEL-NUC.7, Q-M8.7
unnamed: INTEL-NUC.8, Q-M8.8
unnamed: M8/9-13.1, NMEA/PPS.1
unnamed: M8/9-13.2, NMEA/PPS.2
unnamed: M8/9-13.3, NMEA/PPS.3
unnamed: LED.1, R1.2
POWER+: C1.1 (+), C2.1, LED.2, M8/POWER.2, M8/POWER.4, POWER_PCB.2, POWER_PCB.4

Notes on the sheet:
PPS-PPs/NMEA GND-NMEA

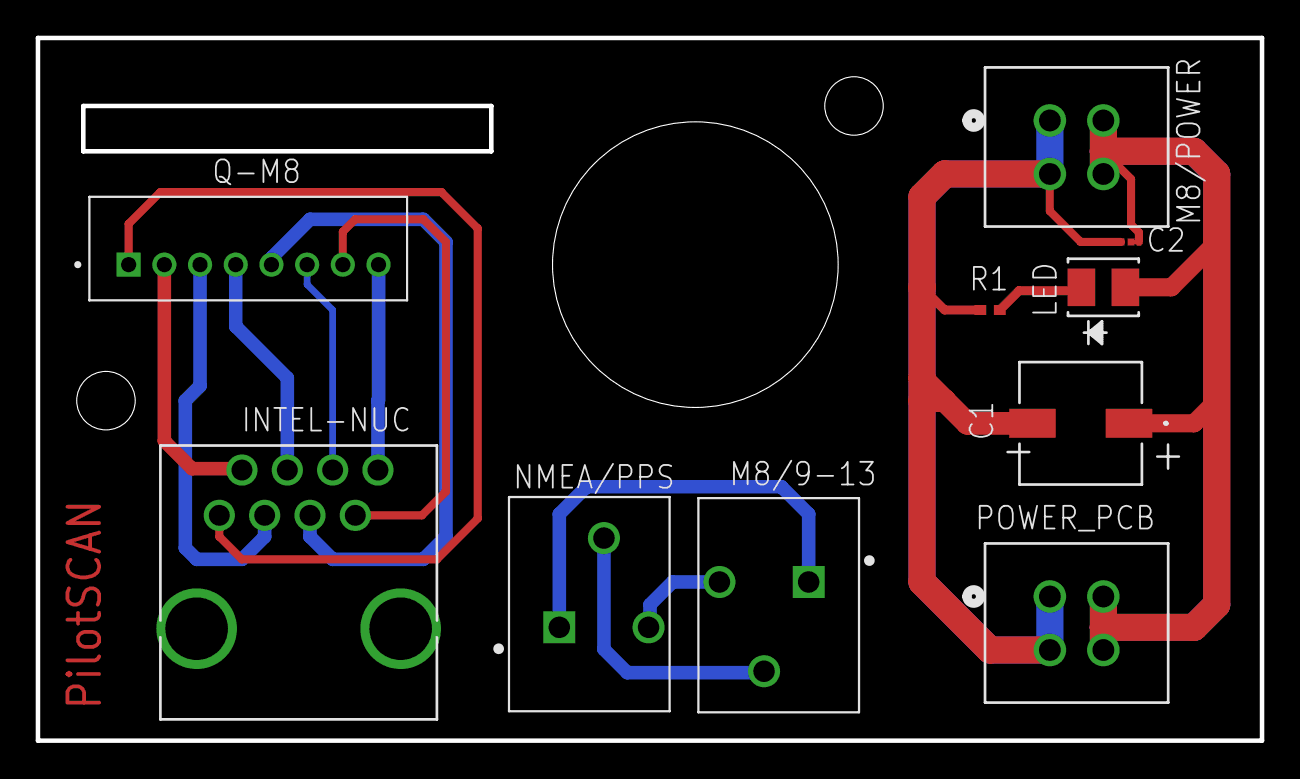
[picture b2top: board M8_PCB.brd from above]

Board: 2 copper layers, 68.6 x 39.4 mm, 10 parts (0 on the bottom side), 14 nets.

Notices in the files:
parts and their libraries:
SparkFun-Aesthetics: Licensing: Creative Commons ShareAlike 4.0 International - https://creativecommons.org/licenses/by-sa/4.0
SparkFun-Aesthetics: Licensing: CC v3.0 Share-Alike You are welcome to use this library for commercial purposes.
